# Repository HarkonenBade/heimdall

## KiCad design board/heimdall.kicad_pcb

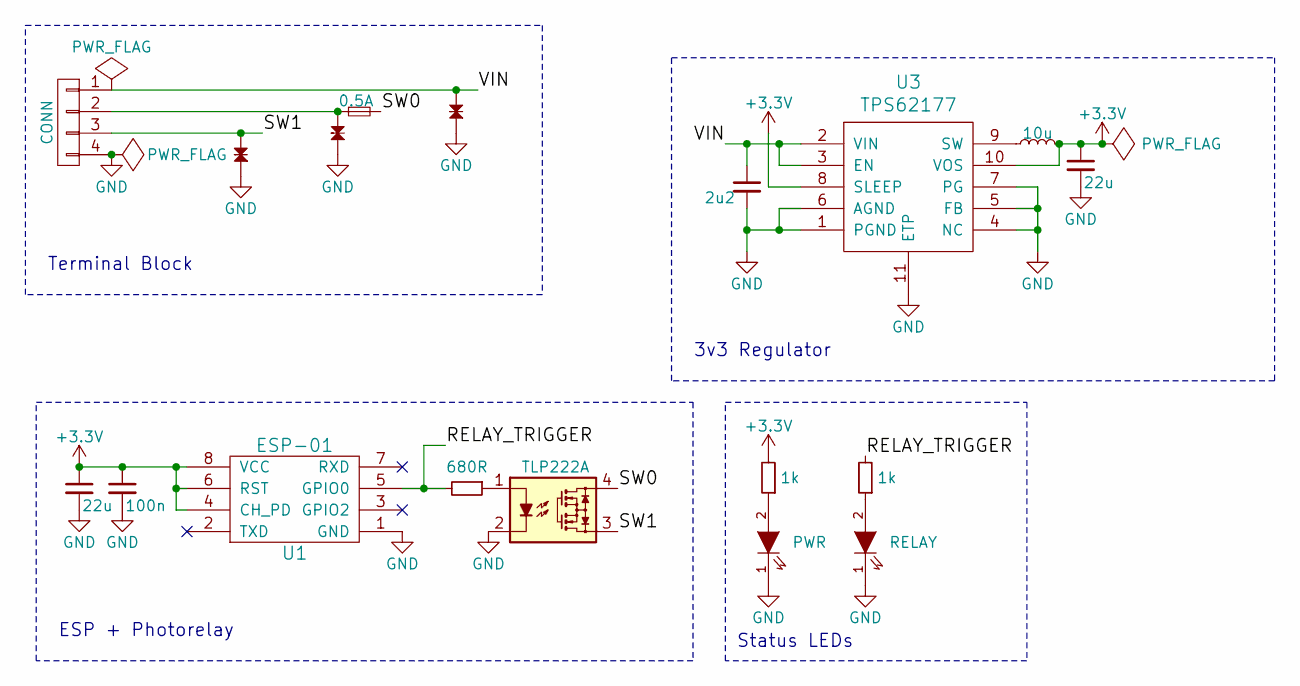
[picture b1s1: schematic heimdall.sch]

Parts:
C1, C5: 22u; 0603; Farnell 2494232
C4: 100n; 0603; Farnell 2524817
C6: 2u2; 0603; Farnell 1845734
D1: TVS_Small; 0603; Farnell 2368174
D2: PWR; 0603-LED; Farnell 2290329
D3, D4: TVS_Small; DO-214AC-SMA; Farnell 1749308
D5: RELAY; 0603-LED; Farnell 2290329
F1: 0.5A; 1206; Farnell 1843802
L1: 10u; WE-TPC; Farnell 1869745
P1: CONN; MKDS-4; Farnell 2314975
R1: 680R; 0603; Farnell 9331441
R2, R3: 1k; 0603; Farnell 9330380
U1: ESP-01; ESP-01-NoSilk; Farnell 1593489
U2: TLP222A; DIP-4_W7.62mm_LongPads; Farnell 1761595
U3: TPS62177; WSON-10; Farnell 2255014

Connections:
+3V3: C1.1, C4.1, C5.1, L1.2, R2.2, U1.4 (CH_PD), U1.6 (RST), U1.8 (VCC), U3.8 (SLEEP), U3.10 (VOS)
/RELAY_TRIGGER: R1.2, R3.2, U1.5 (GPIO0)
/SW0: F1.2, U2.4
/SW1: D4.1 (K), P1.3, U2.3
/VIN: C6.1, D1.1 (K), P1.1, U3.2 (VIN), U3.3 (EN)
GND: C1.2, C4.2, C5.2, C6.2, D1.2 (A), D2.1 (K), D3.2 (A), D4.2 (A), D5.1 (K), P1.4, U1.1 (GND), U2.2, U3.1 (PGND), U3.4 (NC), U3.5 (FB), U3.6 (AGND), U3.7 (PG), U3.11 (ETP)
unnamed: D2.2 (A), R2.1
unnamed: D3.1 (K), F1.1, P1.2
unnamed: D5.2 (A), R3.1
unnamed: L1.1, U3.9 (SW)
unnamed: R1.1, U2.1

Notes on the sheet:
Terminal Block
3v3 Regulator
ESP + Photorelay
Status LEDs

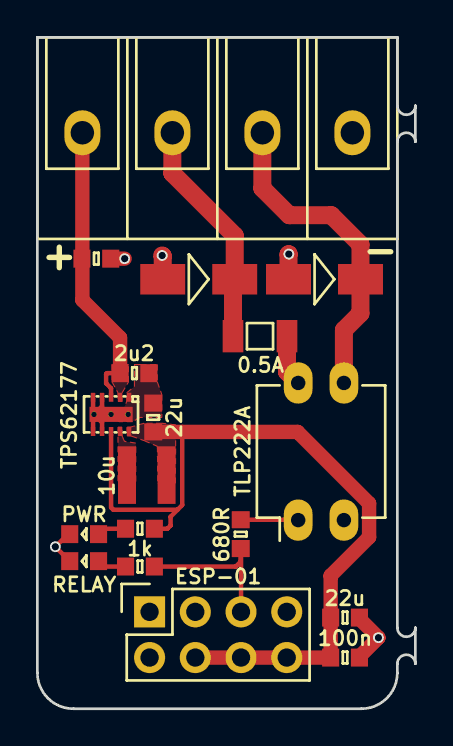
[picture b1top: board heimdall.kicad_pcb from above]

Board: 2 copper layers, 21.0 x 37.3 mm, 18 parts (0 on the bottom side), 11 nets.

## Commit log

2016-05-16 INIT
2016-05-17 Additional faffing, starting PCB
2016-05-17 Updated some componants and shuffled PCB
2016-05-18 Slight schematic faffing, more PCB juggling and sexification.
2016-06-08 Much faffing, many switch mode supply, very PCB.
2016-06-08 Removing some files that got accidentally caught
2016-06-08 ESP lib swallowed by hark-kicad.
2016-06-08 Update terminal block model.
2016-06-08 Various shuffling
2016-06-09 More faffing
2016-06-09 Unbefuckle
2016-06-09 More fix
2016-06-09 PMOS NMOS fun
2016-06-09 Comments based on davids advice
2016-06-09 Missing track
2016-06-14 Minor shuffling and finishing up.
2016-06-27 Various shuffling
    * Switched to agg footprints where possible
    * Farnell numbers and data sheets
    * Status LEDs for dev
    * Schematic shuffling
2016-06-27 Various
    * changed TVS diodes over to new agg:SMA
    * Swapped terminal block for one from HL
    * Setup for board panelizing
2017-06-04 Move board stuff into subdir
2017-06-04 Tweak gitignore
2017-06-04 First bits for firmware
2017-06-04 Fail fallback to webrepl
2017-06-04 More robust error handling
2017-06-05 HTTP server must send connection header
2017-06-06 Fix up a few minor bugs
2017-06-06 Tweak main request routing slightly
2017-06-06 Add to .gitignore
2017-06-06 Switch to picoweb framework in the hope of avoiding socket fail
